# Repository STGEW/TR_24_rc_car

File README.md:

# What's inside?
It's a project with a self build RC car. The project doesn't pretend to be a production ready, but is done for educational purposes.

It has two major parts - a car itself + remote controller.
The project covers:
1) a hardware design of the car and RC - PCB, components, etc
2) a software done in C (TBH it's C++, but only a tiny set of features was used) and in Micropython. They are interchangable and should work on the same set of the hardware.

# Car
A car is built on the platform ordered on the well known web site. The platform has frame done with plexiglass + 4 motos with wheels.
TBD - insert an image

# RC
RC is build with 2 joysticks. Each joystick can be moved in one direction (for the convenience).
TBD - insert an image

# Communication
Communication is done with 2 tranceivers via RF channel. A protocol is extremely simple.

# Freertos part
The code is written on C with Freertos OS. For technical details please check ./freertos_code/README.md

# BOM
Joysticks - KY-023 - 2 items
Battery for car - LiPo battery DC-12300 (12V 3000 mAh)
Batteries for RC - 4 AA type batteries. I'm using 4 Ni-MH accumulators. Can be recharged.
DC-DC converter - MINI-360 DC-DC buck converter (step down). You need 3 of them for converting input voltage to 5V or 3.3V
Motor driver - tb6612fng motor driver
MCU - Paspberry pi PICO W - 2 items (one for car, one for RC)
Motors - 4 of them, they are in a set with car frame

# PCB
Done with a Kicad. Please check ./pcb_design/car_pcb directory with project. ./pcb_design/to_factory contains gerber files generated from the project.

visual diagram done with draw.io explains in a user-friendly way how everything is connected together. - ./pcb_design/diagram.drawio

TBD - inser couple of images

# 3D models
TBD - insert couple of images

# Resources
Contains useful pdf files and images

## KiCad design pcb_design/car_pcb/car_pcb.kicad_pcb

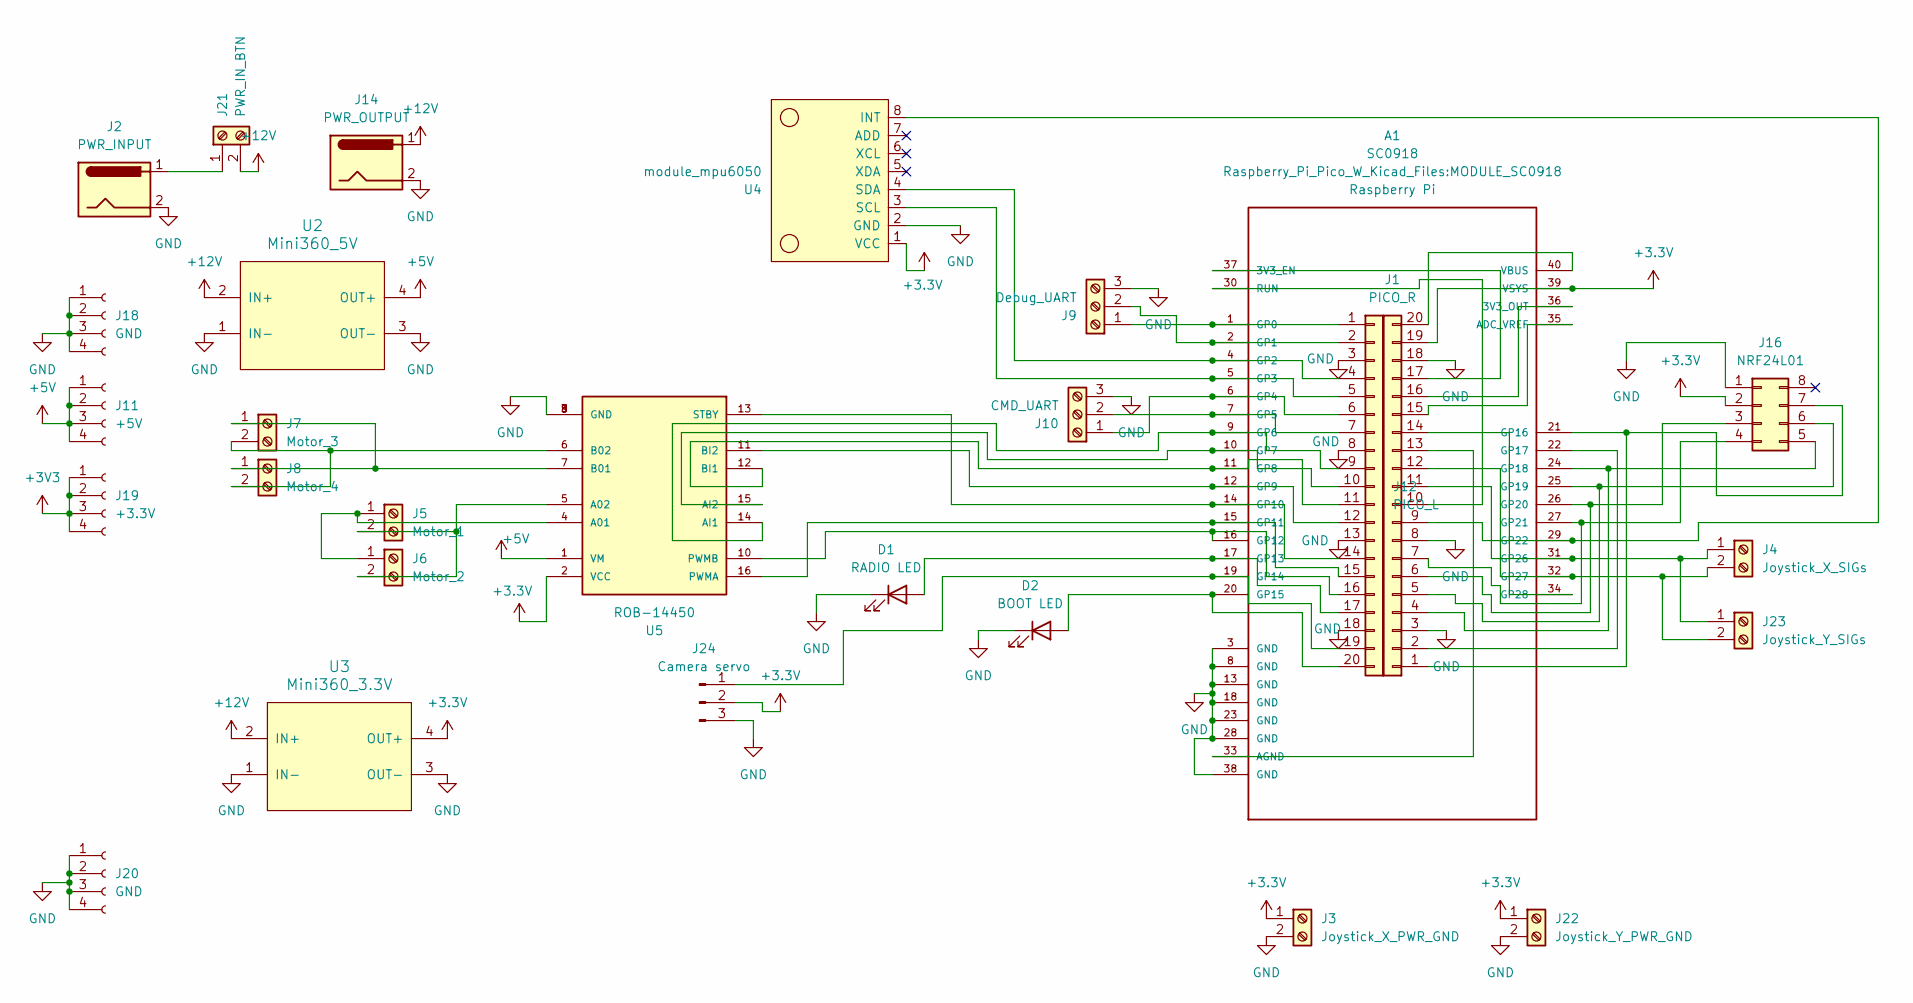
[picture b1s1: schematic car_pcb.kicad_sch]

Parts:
A1: SC0918; MODULE_SC0918; PARTREV 1.6
D1: RADIO LED; LED_D5.0mm
D2: BOOT LED; LED_D5.0mm
J1: PICO_R; PinHeader_1x20_P2.54mm_Vertical
J2: PWR_INPUT; BarrelJack_Horizontal
J3: Joystick_X_PWR_GND; TerminalBlock_Phoenix_MKDS-1,5-2-5.08_1x02_P5.08mm_Horizont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
J4: Joystick_X_SIGs; TerminalBlock_Phoenix_MKDS-1,5-2-5.08_1x02_P5.08mm_Horizont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
J5: Motor_1; TerminalBlock_Phoenix_MKDS-1,5-2-5.08_1x02_P5.08mm_Horizont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
J6: Motor_2; TerminalBlock_Phoenix_MKDS-1,5-2-5.08_1x02_P5.08mm_Horizont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
J7: Motor_3; TerminalBlock_Phoenix_MKDS-1,5-2-5.08_1x02_P5.08mm_Horizont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
J8: Motor_4; TerminalBlock_Phoenix_MKDS-1,5-2-5.08_1x02_P5.08mm_Horizont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
J9: Debug_UART; TerminalBlock_Phoenix_MKDS-1,5-3-5.08_1x03_P5.08mm_Horizont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
J10: CMD_UART; TerminalBlock_Phoenix_MKDS-1,5-3-5.08_1x03_P5.08mm_Horizont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
J11: +5V; PinSocket_1x04_P2.54mm_Vertical
J12: PICO_L; PinHeader_1x20_P2.54mm_Vertical
J14: PWR_OUTPUT; BarrelJack_Horizontal
J16: NRF24L01; PinSocket_2x04_P2.54mm_Vertical
J18, J20: GND; PinSocket_1x04_P2.54mm_Vertical
J19: +3.3V; PinSocket_1x04_P2.54mm_Vertical
J21: PWR_IN_BTN; TerminalBlock_Phoenix_MKDS-1,5-2-5.08_1x02_P5.08mm_Horizont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
J22: Joystick_Y_PWR_GND; TerminalBlock_Phoenix_MKDS-1,5-2-5.08_1x02_P5.08mm_Horizont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
J23: Joystick_Y_SIGs; TerminalBlock_Phoenix_MKDS-1,5-2-5.08_1x02_P5.08mm_Horizont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
J24: Camera servo; PinHeader_1x03_P2.54mm_Vertical
U2: Mini360_5V; Mini360_step-down
U3: Mini360_3.3V; Mini360_step-down
U4: module_mpu6050
U5: ROB-14450; MODULE_ROB-14450; PARTREV 11-13-17

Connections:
+3.3V: A1.39 (VSYS), J1.19, J3.1, J16.2, J22.1, J24.2, U3.4 (OUT+), U4.1 (VCC), U5.2 (VCC)
+3V3: J19.1, J19.2, J19.3, J19.4
+5V: J11.1, J11.2, J11.3, J11.4, U2.4 (OUT+), U5.1 (VM)
+12V: J14.1, J21.2, U2.2 (IN+), U3.2 (IN+)
GND: A1.3 (GND), A1.8 (GND), A1.13 (GND), A1.18 (GND), A1.23 (GND), A1.28 (GND), A1.38 (GND), D1.1 (K), D2.1 (K), J1.3, J1.8, J1.18, J2.2, J3.2, J9.3, J10.3, J12.3, J12.8, J12.13, J12.18, J14.2, J16.1, J18.1, J18.2, J18.3, J18.4, J20.1, J20.2, J20.3, J20.4, J22.2, J24.3, U2.1 (IN-), U2.3 (OUT-), U3.1 (IN-), U3.3 (OUT-), U4.2 (GND), U5.3 (GND), U5.8 (GND), U5.9 (GND)
unnamed: A1.37 (3V3_EN), J1.17
unnamed: A1.36 (3V3_OUT), J1.16
unnamed: A1.35 (ADC_VREF), J1.15
unnamed: A1.33 (AGND), J1.13
unnamed: A1.1 (GP0), J9.1, J12.1
unnamed: A1.2 (GP1), J9.2, J12.2
unnamed: A1.4 (GP2), J12.4, U4.4 (SDA)
unnamed: A1.5 (GP3), J12.5, U4.3 (SCL)
unnamed: A1.6 (GP4), J10.1, J12.6
unnamed: A1.7 (GP5), J10.2, J12.7
unnamed: A1.9 (GP6), J12.9, U5.14 (AI1)
unnamed: A1.10 (GP7), J12.10, U5.15 (AI2)
unnamed: A1.11 (GP8), J12.11, U5.12 (BI1)
unnamed: A1.12 (GP9), J12.12, U5.11 (BI2)
unnamed: A1.14 (GP10), J12.14, U5.13 (STBY)
unnamed: A1.15 (GP11), J12.15, U5.16 (PWMA)
unnamed: A1.16 (GP12), J12.16, U5.10 (PWMB)
unnamed: A1.17 (GP13), D1.2 (A), J12.17
unnamed: A1.19 (GP14), J12.19, J24.1
unnamed: A1.20 (GP15), D2.2 (A), J12.20
unnamed: A1.21 (GP16), J1.1, J16.7
unnamed: A1.22 (GP17), J1.2
unnamed: A1.24 (GP18), J1.4, J16.5
unnamed: A1.25 (GP19), J1.5, J16.6
unnamed: A1.26 (GP20), J1.6, J16.3
unnamed: A1.27 (GP21), J1.7, J16.4
unnamed: A1.29 (GP22), J1.9, U4.8 (INT)
unnamed: A1.31 (GP26), J1.11, J4.1, J23.1
unnamed: A1.32 (GP27), J1.12, J4.2, J23.2
unnamed: A1.34 (GP28), J1.14
unnamed: A1.30 (RUN), J1.10
unnamed: A1.40 (VBUS), J1.20
unnamed: J5.1, J6.1, U5.4 (A01)
unnamed: J5.2, J6.2, U5.5 (A02)
unnamed: J7.1, J8.1, U5.7 (B01)
unnamed: J7.2, J8.2, U5.6 (B02)
unnamed: J2.1, J21.1

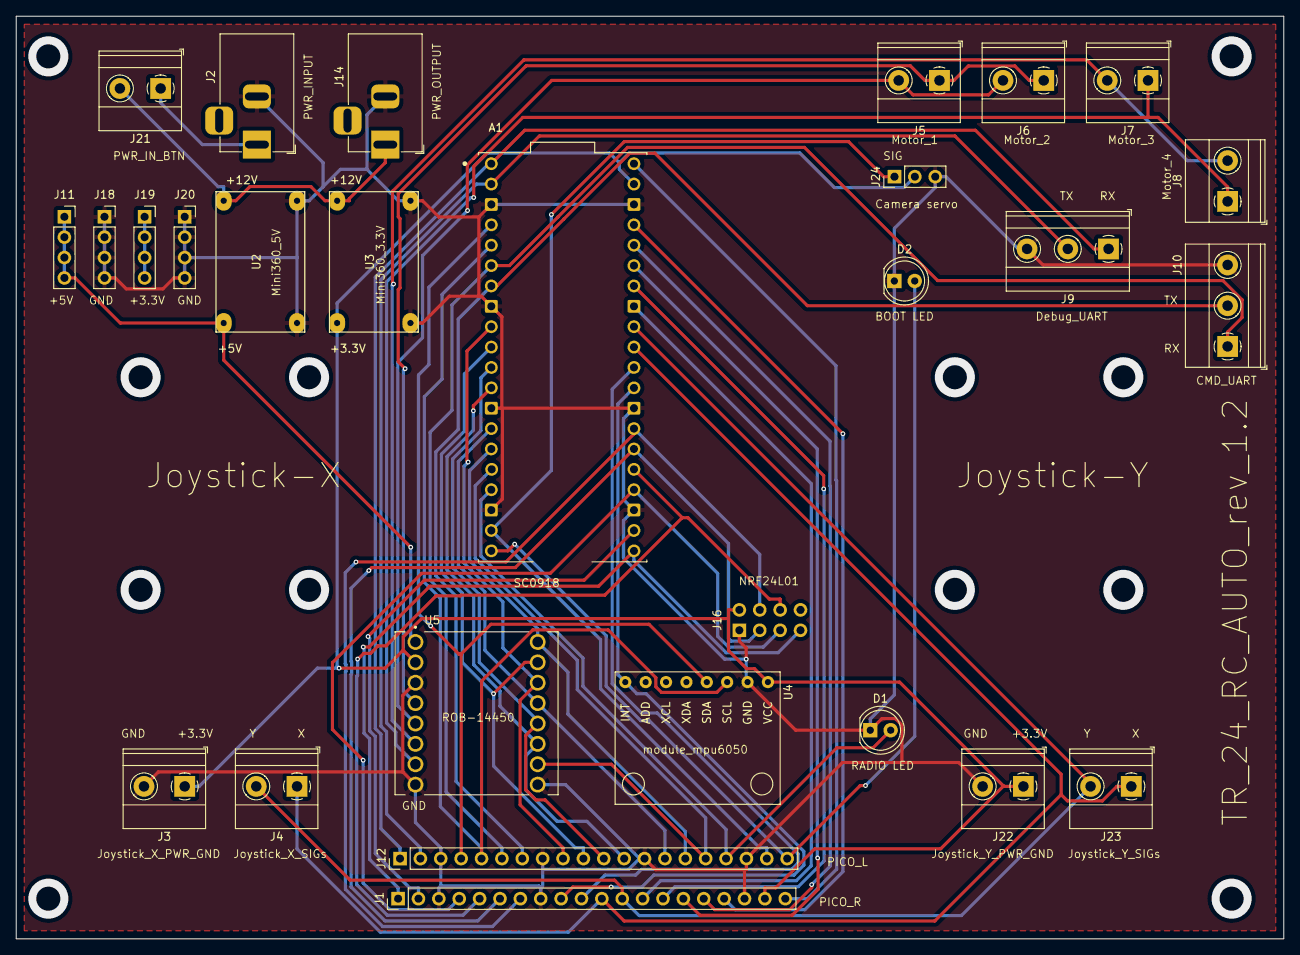
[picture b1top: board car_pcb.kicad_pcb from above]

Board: 2 copper layers, 158.0 x 115.0 mm, 28 parts (1 on the bottom side), 42 nets.

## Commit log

2024-05-05 update girignore
2024-05-05 add 3D models
2024-05-05 add diagrams
2024-05-05 add freertos code
2024-05-05 add pcb design
2024-05-05 add resources
2024-05-05 add microphython
2024-05-17 update pcbs
2024-06-02 Update README, fix build for RC part
2024-06-05 fix build system and fix differences in pins between RC and AUTO
2024-06-06 update README files and CMake files
2024-06-09 Make a generic diagram for both RC and Auto Add several resources Update README.md file
2024-06-09 fix issue with mistakes in rev 1.1. Now rev 1.2 is ready
2024-06-09 fix a bug with wrong BRAKE code
2024-06-09 add some code for micropython
2024-06-10 rework C/C++ code
2024-06-12 start to work on micropython part
2024-06-23 micropython debugging
2024-06-23 update README part regarding micropython
2024-06-25 save progress
2024-06-30 save the progress
2024-07-07 in progress
2024-07-12 add pid controller class
2024-07-14 add plexiglass cutting files
2024-07-16 update plexiglass layout, remove garbage
2024-07-16 fix odometer part, fix bugs
2024-07-17 remove not required files
2024-07-17 now odometer works
2024-08-20 fix odometry
2024-08-25 remove obsolete code from diff vehicle
2024-08-25 clean python part for motion
2024-08-25 clean obsolete code
2024-09-03 support message with odometry
2024-09-19 update micropython part
2024-09-19 Fix issue with not initialized pointer change frequency of the PV msg Output PV msg only during several states
2024-10-05 remove micropython part
2024-11-06 Manually initialize UART0 for car and rc Change UART0 baudrate from the default value 115200 to more logical 460800 for car and rc
